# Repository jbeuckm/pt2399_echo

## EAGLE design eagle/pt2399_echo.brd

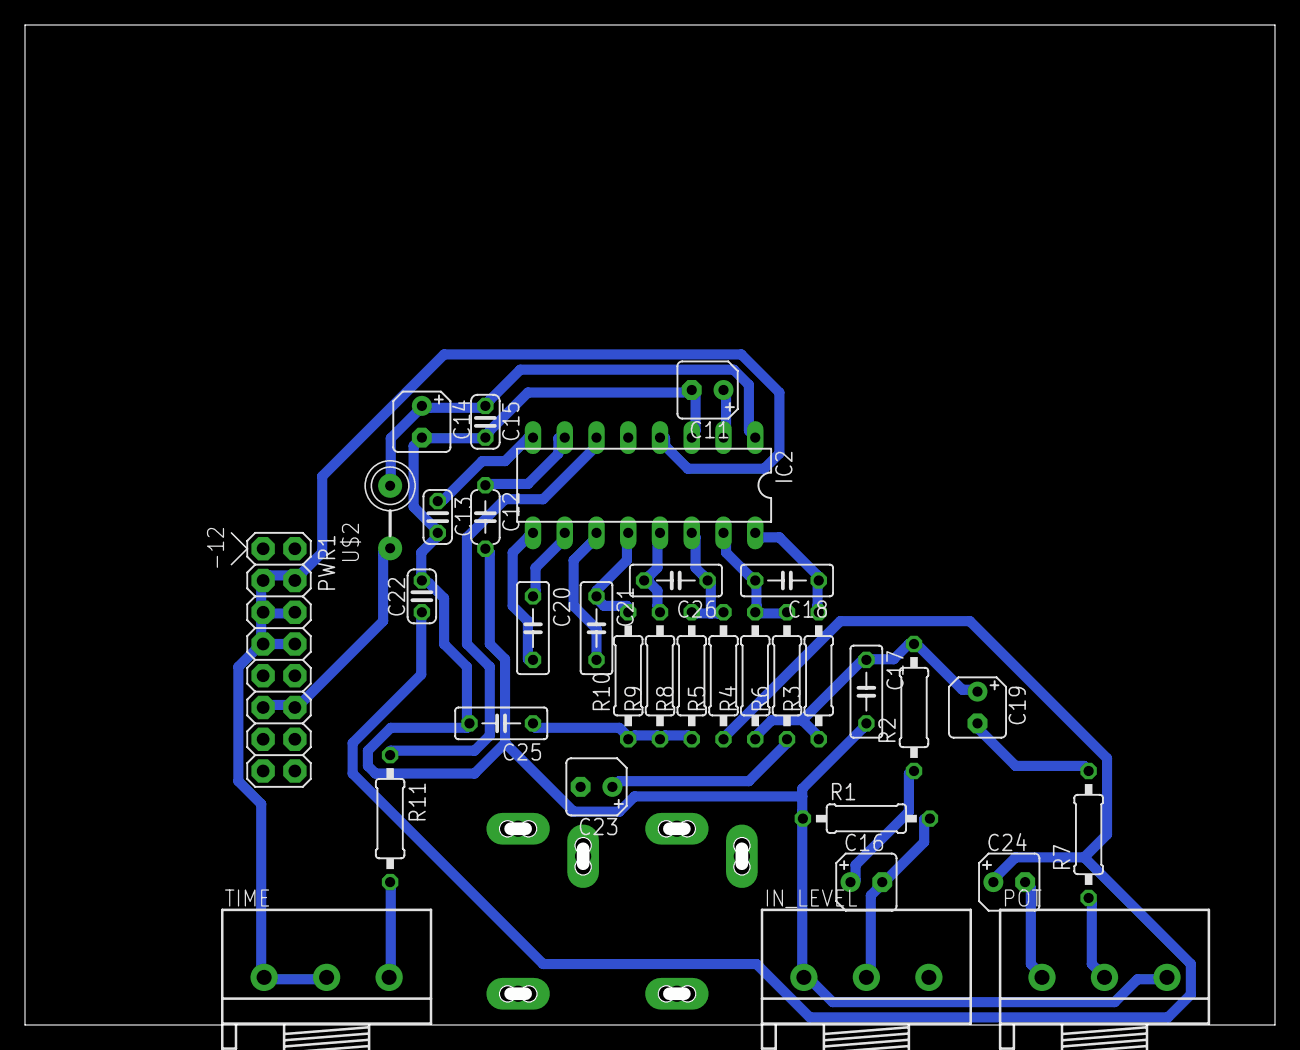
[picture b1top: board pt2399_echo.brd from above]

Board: 2 copper layers, 99.0 x 79.0 mm, 35 parts (0 on the bottom side), 28 nets.

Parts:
C11: 47u; B45181A
C12: 100n; C050-024X044
C13, C15: 100n; C025-024X044
C14: 100u; B45181A
C16, C19: 4u7; B45181A
C17: 3n9; C050-025X075
C18, C26: 560p; C050-025X075
C20, C21: 82n; C050-025X075
C22: 10n; C025-024X044
C23, C24: 10u; B45181A
C25: 3n3; C050-025X075
IC2: DIP16
INPUT: AUDIO-JACK; ERTHENVAR-JACK-90DEG
IN_LEVEL: 100k; 3RP/1610N
OUT: AUDIO-JACK; ERTHENVAR-JACK-90DEG
POT: 50k; 3RP/1610N
PWR1: POWER; POWER_16
R1: 100k; 0207/10
R2, R8: 15k; 0207/10
R3, R4, R9, R10, R11: 10k; 0207/10
R5: 5k6; 0207/10
R6: 4k7; 0207/10
R7: 18k; 0207/10
TIME: 20k; 3RP/1610N
U$2: FB

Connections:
+5V: C14.+, C15.1, IC2.1, U$2.P$2
AGND: C11.-, C12.2, C13.2, C14.-, C15.2, C17.2, C22.2, C25.2, IC2.3, INPUT.P$1, IN_LEVEL.1, OUT.P$1, POT.3, R1.1
GND: IC2.4, PWR1.3, PWR1.4, PWR1.5, PWR1.6, PWR1.7, PWR1.8, TIME.1, TIME.2
unnamed: PWR1.11, PWR1.12, U$2.P$1
unnamed: C23.+, R6.1
unnamed: C12.1, IC2.7
unnamed: C13.1, IC2.8
unnamed: INPUT.P$3, IN_LEVEL.3
unnamed: C11.+, IC2.2
unnamed: C16.+, R2.1
unnamed: C16.-, IN_LEVEL.2, R1.2
unnamed: C18.2, IC2.15, R4.2, R6.2
unnamed: C18.1, IC2.16, R3.2
unnamed: C17.1, C19.+, R2.2, R3.1, R4.1
unnamed: C20.2, IC2.9
unnamed: C20.1, IC2.10
unnamed: C21.2, IC2.11
unnamed: C23.-, OUT.P$3
unnamed: C26.1, IC2.14, R5.2, R8.2
unnamed: C19.-, R7.2
unnamed: POT.2, R7.1
unnamed: C22.1, C24.+, R5.1
unnamed: C24.-, POT.1
unnamed: C21.1, IC2.12, R10.2
unnamed: C26.2, IC2.13, R9.2
unnamed: C25.1, R8.1, R9.1, R10.1
unnamed: R11.2, TIME.3
unnamed: IC2.6, R11.1

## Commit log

2016-02-07 just about routed
2016-07-04 corrected, rerouted, gcode
2016-10-24 started a panel for the echo
